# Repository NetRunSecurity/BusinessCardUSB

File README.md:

# USB Business Card (CH552G)

A real, working USB business card. It's shaped like a card, but the bottom edge is
cut into a USB-A male connector, plug it straight into any port, no cable, no
adapter. Powered by a **CH552G** with **native USB** (no USB-to-serial bridge chip),
two **capacitive touch** pads, a status LED, and a UART debug header.

It's a business card, a hacking tool, and a flex in one.

📖 Full build write-up, schematics and pinout:
**<https://wiki.netrunsecurity.com/electronics/sao/business-card/>**

---

## What's in this repo

```
.
├─ hardware/
│  ├─ card/
│  │  ├─ v4/          # current editable KiCad design (source of truth)
│  │  └─ v3/          # validated production build, gerbers only
│  └─ shim/           # USB-tab PCB shim (KiCad source + gerbers)
├─ firmware/
│  ├─ rubber-ducky/   # HID keystroke injection (opens a URL on plug-in)
│  ├─ touchpad-testing/ # capacitive Touch-Key + LED demo
│  ├─ ctf/            # USB serial CLI with hidden flags
│  └─ usb-uart-bridge/ # USB ↔ UART bridge for debugging IoT targets
├─ docs/              # photos, schematic PDF, fabrication files (BOM)
├─ LICENSE            # TAPR OHL 1.0, hardware
└─ firmware/LICENSE   # GPL-3.0, firmware
```

## Versions

| Version | Status | Files |
| --- | --- | --- |
| **V3** | Soldered & tested, the build in the photos | Gerbers (archived) |
| **V4** | Same circuit, current revision | Full KiCad sources |

V3 and V4 are **electrically identical**. R6 was a redundant RST pull-down (R5
already pulls RST to VCC) and was left unpopulated on V3, so it never affected the
circuit. V4 removes the footprint to prevent accidental population and updates the
silkscreen text. The V4 sources faithfully represent the validated V3 build.

> ⚠️ The original `v00110100` board had a reversed USB edge-connector polarity that
> destroyed chips on plug-in. **Do not fabricate that revision.** Use V3/V4.

## Hardware

- **MCU:** WCH CH552G (8051 core, native USB)
- **USB:** PCB-edge USB-A male connector, no bridge IC
- **Input:** 2× capacitive Touch-Key pads (read through the solder mask)
- **Indicator:** status LED
- **Debug / flash:** 1×4 UART header + BOOT/RESET buttons
- **Mechanical:** card + glued USB-tab shim (~2.4 mm total) for a snug USB-A fit
- **EDA:** KiCad

## Bill of Materials

| Ref | Qty | Value / Part | Package | MPN | LCSC |
| --- | --- | --- | --- | --- | --- |
| U1 | 1 | CH552G — 8-bit USB MCU | SOP-16 | CH552G | [C111292](https://www.lcsc.com/product-detail/C111292.html) |
| C1 | 1 | 10 µF 16 V X5R | 0805 | CL21A106KOQNNNE | [C1713](https://www.lcsc.com/product-detail/C1713.html) |
| C2, C3 | 2 | 100 nF 50 V X7R | 0805 | CC0805KRX7R9BB104 | [C49678](https://www.lcsc.com/product-detail/C49678.html) |
| R1, R2 | 2 | 1 kΩ 1% | 0805 | 0805W8F1001T5E | [C17513](https://www.lcsc.com/product-detail/C17513.html) |
| R4, R5 | 2 | 10 kΩ 1% | 0805 | 0805W8F1002T5E | [C17414](https://www.lcsc.com/product-detail/C17414.html) |
| D1 | 1 | Red LED 630 nm | 0805 | NCD0805R1 | [C84256](https://www.lcsc.com/product-detail/C84256.html) |
| SW1, SW2 | 2 | Tactile switch SPST | SMD 5.2×5.2 mm | TL3342F260QG | [C2886894](https://www.lcsc.com/product-detail/C2886894.html) |
| J2 | 1 | 1×4 pin header 2.54 mm (UART) | THT | HX PH254-01-04 | [C52016392](https://www.lcsc.com/product-detail/C52016392.html) |

> R6 is not populated (removed in V4). TP1/TP2 are copper touch pads and U2 is the
> PCB-edge USB connector — neither is a placed part.

## Firmware

Several firmwares, each demoing a different capability of the platform:

- **rubber-ducky**: enumerates as a USB keyboard and types a payload (opens a URL).
- **touchpad-testing**:  exercises the two Touch-Key pads and the LED.
- **ctf**: exposes a USB serial CLI with a small command set and hidden flags.
- **usb-uart-bridge**: bridges the on-board UART to the host for field debugging.

Build & flash instructions are in [`firmware/README.md`](firmware/README.md)
(Arduino IDE 2.x + ch55xduino).

## Fabricate / assemble your own

1. Send the gerbers in `hardware/card/v4/` (or `v3/`) to any fab.
2. Order parts from the assembly BOM in `docs/` (LCSC part numbers included).
3. Glue the shim under the USB tab.
4. Flash a firmware, see `firmware/README.md`.

A few hard-won notes: hand-solder the SOP-16 (no hot air), verify USB edge-pad
polarity against the socket before ordering, and keep a USB power meter handy for
first power-up.

## License

This is open hardware, dual-licensed:

- **Hardware** (PCB design, schematic, gerbers): **TAPR Open Hardware License 1.0**, see [`LICENSE`](LICENSE).
- **Firmware** (code): **GPL-3.0**, see [`firmware/LICENSE`](firmware/LICENSE).

Derivatives welcome, credit the original and highlight your changes.

## Author

Designed by **AlrikRr**, [NetRunSecurity](https://www.netrunsecurity.com) ·
[wiki](https://wiki.netrunsecurity.com) · [linktr.ee](https://linktr.ee/alrikrr)

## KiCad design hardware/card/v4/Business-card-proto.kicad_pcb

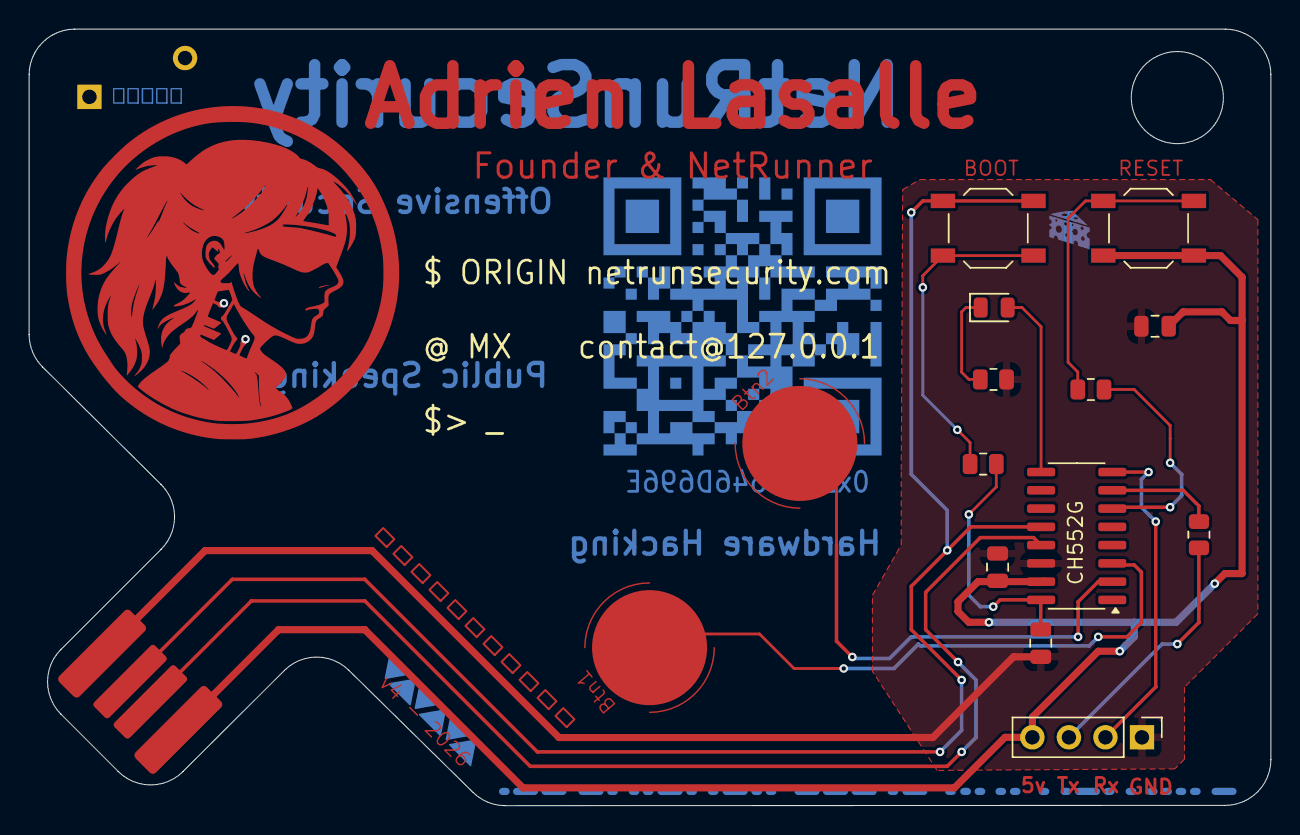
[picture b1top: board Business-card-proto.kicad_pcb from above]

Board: 2 copper layers, 86.3 x 54.0 mm, 15 parts (1 on the bottom side), 15 nets.

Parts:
C1: 10uF; C_0805_2012Metric
C2, C3: 100nF; C_0805_2012Metric
D1: LED; LED_0805_2012Metric
J2: UART; PinHeader_1x04_P2.54mm_Vertical
R1, R2: 1k; R_0805_2012Metric
R4, R5: 10k; R_0805_2012Metric
SW1: SW_RST; SW_SPST_TL3342
SW2: SW_BOOT; SW_SPST_TL3342
TP1, TP2: TouchPad_Circle_10mm
U1: SOIC-16_3.9x9.9mm_P1.27mm
U2: PCB_USB

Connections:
+5V: C1.1, C2.1, J2.4, SW1.2, U1.15 (VCC), U2.1 (Vcc)
GND: C1.2, C2.2, C3.2, J2.1, R2.2, U1.14 (GND), U2.4 (GND)
unnamed: D1.2 (A), U1.9 (P1.1)
unnamed: D1.1 (K), R2.1
unnamed: J2.2, U1.8 (RXD)
unnamed: J2.3, R1.2
unnamed: R4.1, SW2.2
unnamed: R5.1, SW1.1
unnamed: TP1.1 (PAD), U1.3 (MOSI)
unnamed: TP2.1 (PAD), U1.2 (P1.4)
unnamed: R5.2, U1.6 (RST)
unnamed: R1.1, U1.7 (TXD)
unnamed: SW2.1, U1.12 (UD+), U2.3 (D+)
unnamed: U1.13 (UD-), U2.2 (D-)
unnamed: C3.1, R4.2, U1.16 (V33)

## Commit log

2026-06-11 full doc + v3 & v4 gerber
2026-06-11 Pic of sodlered v3
